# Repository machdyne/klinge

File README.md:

# Klinge Computer

Klinge is an FPGA computer designed by Lone Dynamics Corporation.

This repo contains schematics, PCB layouts, pinouts, a 3D-printable case, example gateware and documentation.

The 3D enclosure fits into a [Half10](https://github.com/machdyne/half10) compute bay, which can be used stand-alone or attached to a 10" rack.

Find more information on the [Klinge product page](https://machdyne.com/product/klinge-computer/).

## Programming Klinge

Klinge has a JTAG interface and ships with a [DFU bootloader](https://github.com/machdyne/tinydfu-bootloader) that allows the included flash [MMOD](https://machdyne.com/product/mmod) to be programmed over the USB-C port.

### DFU

The DFU bootloader is available for 5 seconds after power-on, issuing a DFU command during this period will stop the boot process until the DFU device is detached. If no command is received the boot process will continue and the user gateware will be loaded.

Install [dfu-util](http://dfu-util.sourceforge.net) (Debian/Ubuntu):

```
$ sudo apt install dfu-util
```

Update the user gateware on the flash MMOD:

```
$ sudo dfu-util -a 0 -D image.bit
```

Detach the DFU device and continue the boot process:

```
$ sudo dfu-util -a 0 -e
```

It is possible to update the bootloader itself using DFU but you shouldn't attempt this unless you have a JTAG programmer (or another method to program the MMOD) available, in case you need to restore the bootloader.

### JTAG

These examples assume you're using a "USB Blaster" JTAG cable, see the header pinout below. You will need to have [openFPGALoader](https://github.com/trabucayre/openFPGALoader) installed.

Program the configuration SRAM:

```
openFPGALoader -c usb-blaster image.bit
```

Program the flash MMOD:

```
openFPGALoader -f -c usb-blaster images/bootloader/tinydfu_klinge.bit
```

## Blinky 

Building the blinky example requires [Yosys](https://github.com/YosysHQ/yosys), [nextpnr-ecp5](https://github.com/YosysHQ/nextpnr) and [Project Trellis](https://github.com/YosysHQ/prjtrellis).

Assuming they are installed, you can simply type `make` to build the gateware, which will be written to output/blinky.bin. You can then use [openFPGALoader](https://github.com/trabucayre/openFPGALoader) or dfu-util to write the gateware to the device.

## Linux

See the [Kakao Linux](https://github.com/machdyne/kakao) repo for the latest instructions.

### Prebuilt Images

Copy the files from the `images/linux` directory to the root directory of a FAT-formatted MicroSD card.

Klinge ships with LiteX gateware on the user gateware section of the MMOD that is compatible with these images. After several seconds the Linux penguin should appear on the screen (HDMI) followed by a login prompt.

### Building Linux

Please follow the setup instructions in the [linux-on-litex-vexriscv](https://github.com/litex-hub/linux-on-litex-vexriscv) repo and then:

1. Build the Linux-capable gateware:

```
$ cd linux-on-litex-vexriscv
$ ./make.py --board klinge --uart-baudrate 115200 --build

$ ls build/klinge
```

2. Write the gateware to the MMOD using USB DFU:

```
$ sudo dfu-util -a 0 -D build/klinge/gateware/klinge.bit
```

3. Copy the device tree binary `build/klinge/klinge.dtb` to a FAT-formatted MicroSD card.

4. Build the Linux kernel and root filesystem:

See the [Kakao Linux](https://github.com/machdyne/kakao?tab=readme-ov-file#optional-building-kakao-linux) repo for instructions.

5. Copy the Image and rootfs.cpio files generated in the previous step to the boot partition of the MicroSD card, in addition to the following files:

6. Copy the OpenSBI binary (included in this repo as `klinge/images/linux/opensbi.bin`) to the MicroSD card. Alternatively, you can build this binary by following [these instructions](https://github.com/litex-hub/linux-on-litex-vexriscv#-generating-the-opensbi-binary-optional).

7. Copy `klinge/images/linux/boot.json` to the MicroSD card.

8. Power-cycle Klinge. After Linux has finished booting you should see a login prompt on the HDMI display.

## LiteX

### Installing LiteX

If you haven't yet installed LiteX please see the [LiteX quick start guide](https://github.com/enjoy-digital/litex#quick-start-guide) for details on installing LiteX.

### Building Custom Gateware

Build the LiteX gateware:

```
$ cd litex-boards/litex_boards/targets
$ ./machdyne_klinge.py --cpu-type=vexriscv --cpu-variant=lite --sys-clk-freq 40000000 --uart-baudrate 1000000 --uart-name serial --build
```

Program the LiteX gateware to SRAM over JTAG:

```
$ ./machdyne_klinge.py --cable usb-blaster --load
```

Or program the LiteX gateware to flash over DFU:

```
$ sudo dfu-util -a 0 -D build/machdyne_klinge/gateware/machdyne_klinge.bit
```

## JTAG Header

The 3.3V JTAG header can be used to program the FPGA SRAM as well as the MMOD flash memory. It can also be used to provide power (5V) to the board.

```
2 4 6
1 3 5
```

| Pin | Signal |
| --- | ------ |
| 1 | TCK |
| 2 | TDI |
| 3 | TDO |
| 4 | TMS |
| 5 | 5V0 |
| 6 | GND |

## Board Revisions

| Revision | Notes |
| -------- | ----- |
| V1 | Current production version |

## License

The contents of this repo are released under the [Lone Dynamics Open License](LICENSE.md).

Note: You can use these designs for commercial purposes but we ask that instead of producing exact clones, that you either replace our trademarks and logos with your own or add your own next to ours.

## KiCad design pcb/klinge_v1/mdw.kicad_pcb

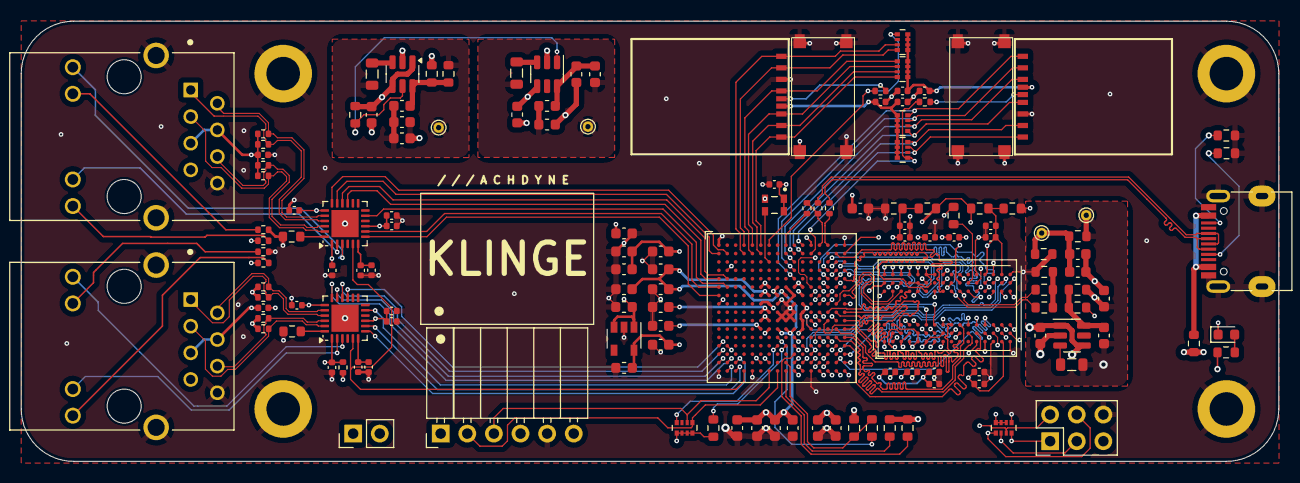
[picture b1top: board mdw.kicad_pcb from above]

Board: 6 copper layers, 120.0 x 42.0 mm, 143 parts (0 on the bottom side), 145 nets.

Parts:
C1, C2, C3, C4, C5, C6, C8, C9, C10, C13: 220nF; C_0603_1608Metric
C7, C11, C12, C15, C43: 1uF; C_0603_1608Metric
C14, C44, C48, C50, C54: 4.7uF; C_0603_1608Metric
C16, C64: 10uF; C_0402_1005Metric
C17, C19, C21, C22, C23, C26, C27, C32, C34, C35, C36, C37, C39, C47, C53, C59, C65: 100nF; C_0402_1005Metric
C18, C24, C29, C30, C33, C38, C41, C57: 1uF; C_0402_1005Metric
C20, C49: 470pF; C_0402_1005Metric
C25, C31: 22uF; R_0603_1608Metric
C28: 100nF; R_0603_1608Metric
C40, C60: 22nF; C_0402_1005Metric
C42: 100nF; C_0603_1608Metric
C45, C52, C61: 10pF; C_0603_1608Metric
C46, C56: 10uF; C_0603_1608Metric
C51, C55, C58, C62, C63: 22uF; C_0603_1608Metric
D1: LED; LED_0603_1608Metric
FB1, FB3, FB4: FerriteBead_Small; R_0603_1608Metric
FB2: FerriteBead_Small; R_0402_1005Metric
H1, H2, H3, H4: MountingHole_Pad; MountingHole_3.2mm_M3_ISO14580_Pad
J1: USB_C_Receptacle_USB2.0_14P; USB_C_Receptacle_HRO_TYPE-C-31-M-12-BIG-PADS-PASTE
J2, J4: MICROSD; TF-018B-H15-HAND-SOLDER
J3, J5: HR911105A; HANRUN_HR911105A
J6: Conn_01x02_Pin; PinHeader_1x02_P2.54mm_Vertical
JTAG1: Conn_02x03_Top_Bottom; PinHeader_2x03_P2.54mm_Vertical
L1, L2, L3: INDUCTOR; L_0805_2012Metric
MMOD1: PMOD-Device-x1-Type-2-SPI; MMOD_Host_Socket
R1, R2, R3: 4K7; R_0603_1608Metric
R4, R39, R40: 1K; R_0603_1608Metric
R6: 200K; R_0603_1608Metric
R7: 44K2; R_0603_1608Metric
R8, R47: 100R; R_0402_1005Metric
R9, R20, R21: 51R; R_0603_1608Metric
R11: 1K5; R_0603_1608Metric
R12, R31: 5K1; R_0603_1608Metric
R14: 240R; R_0603_1608Metric
R29: 536R; R_0603_1608Metric
R30, R59: 12K1; R_0603_1608Metric
R32, R33: 22R; R_0402_1005Metric
R34: 1K5; R_0402_1005Metric
R45: 150K; R_0603_1608Metric
R46, R53: 120K; R_0603_1608Metric
R51, R54, R55, R56, R60, R61, R62, R63: 49R9; R_0402_1005Metric
R52: 100K; R_0603_1608Metric
R57, R58, R64, R65: 536R; R_0402_1005Metric
RN1: 4K7; R_Array_Convex_4x0402
RN2, RN3, RN5, RN6: 20K; R_Array_Convex_4x0402
RN4: 10K; R_Array_Convex_4x0402
TP2: TP_DRAM_VREF; TestPoint_THTPad_D1.0mm_Drill0.5mm
TP3: TP_PWR1V35; TestPoint_THTPad_D1.0mm_Drill0.5mm
TP4: TP_PWR1V1; TestPoint_THTPad_D1.0mm_Drill0.5mm
TP5: TP_PWR3V3; TestPoint_THTPad_D1.0mm_Drill0.5mm
U1: Lattice_ECP_FPGA_ECP5U_45_CABGA256; BGA-256_14.0x14.0mm_Layout16x16_P0.8mm_Ball0.45mm_Pad0.32mm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
U3: MT41K64M16TW-107_J-TR; BGA-96_9.0x13.0mm_Layout2x3x16_P0.8mm_FIXED_SILK
U4, U5, U6: TLV62568DDC; SOT-23-6
U7, U10: LAN8720A; QFN-24-1EP_4x4mm_P0.5mm_EP2.6x2.6mm
U8: TLV73325PDBV; SOT-23-5
Y1: KC2016Z48; OSC_KC2016Z13.5600C1KX00

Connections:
/CFG_1: R1.2, U1.P10 (CFG_1)
/CSPI_MISO: MMOD1.3 (SO), RN4.2 (R2.1), U1.T7 (PB11A/+/D1/MISO/IO1)
/CSPI_MOSI: MMOD1.2 (SI), RN4.1 (R1.1), U1.T8 (PB11B/-/D0/MOSI/IO0)
/CSPI_SCK: MMOD1.4 (SCK), R4.2, U1.N9 (CCLK/MCLK/SCK)
/CSPI_SS: MMOD1.1 (SS), RN4.4 (R4.1), U1.N8 (PB15A/+/HOLDN/DI/BUSY/CSSPIN/CEN)
/DRAM_A0: U1.R15 (PR59C/+/RDQ65), U3.N3 (A0)
/DRAM_A1: U1.L13 (PR38C/+/GR_PCLK3_1/RDQ41), U3.P7 (A1)
/DRAM_A2: U1.P14 (PR59B/-/HS/RDQ65), U3.P3 (A2)
/DRAM_A3: U1.R14 (PR62B/-/HS/RDQ65), U3.N2 (A3)
/DRAM_A4: U1.L12 (PR38D/-/RDQ41), U3.P8 (A4)
/DRAM_A5: U1.T14 (PR62D/-/RDQ65), U3.P2 (A5)
/DRAM_A6: U1.N11 (PR68B/-/HS/RDQ65), U3.R8 (A6)
/DRAM_A7: U1.T13 (PR65B/-/HS/RDQSN65), U3.R2 (A7)
/DRAM_A8: U1.P12 (PR68D/-/LRC_GPLL0C_IN/RDQ65), U3.T8 (A8)
/DRAM_A9: U1.T15 (PR59D/-/RDQ65), U3.R3 (A9)
/DRAM_A10: U1.C14 (PR11C/+/RDQ17), U3.L7 (A10/AP)
/DRAM_A11: U1.M13 (PR44C/+/RDQ41), U3.R7 (A11)
/DRAM_A12: U1.E14 (PR14C/+/RDQ17), U3.N7 (A12/BC#)
/DRAM_A13: U1.R13 (PR62C/+/RDQ65), U3.T3 (A13)
/DRAM_A14: U1.M14 (PR41D/-/RDQ41), U3.T7 (A14)
/DRAM_A15: U1.D14 (PR11D/-/RDQ17), U3.M7 (A15)
/DRAM_BA0: U1.N16 (PR41A/+/HS/RDQS41), U3.M2 (BA0)
/DRAM_BA1: U1.K13 (PR38A/+/GR_PCLK3_0/HS/RDQ41), U3.N8 (BA1)
/DRAM_BA2: U1.P16 (PR44A/+/HS/RDQ41), U3.M3 (BA2)
/DRAM_CAS#: U1.M16 (PR35C/+/PCLKT3_0/RDQ41), U3.K3 (CAS#)
/DRAM_CKE: U1.K12 (PR38B/-/HS/RDQ41), U3.K9 (CKE)
/DRAM_CK_N: R21.2, U1.C15 (PR14B/-/HS/RDQ17), U3.K7 (CK#)
/DRAM_CK_P: R20.2, U1.C16 (PR14A/+/HS/RDQ17), U3.J7 (CK)
/DRAM_CS#: U1.M15 (PR35D/-/PCLKC3_0/RDQ41), U3.L2 (CS#)
/DRAM_DQ0: U1.F14 (PR14D/-/RDQ17), U3.E3 (DQ0)
/DRAM_DQ1: U1.E16 (PR20D/-/RDQ17), U3.F7 (DQ1)
/DRAM_DQ2: U1.F12 (PR17D/-/RDQ17), U3.F2 (DQ2)
/DRAM_DQ3: U1.F15 (PR20C/+/RDQ17), U3.F8 (DQ3)
/DRAM_DQ4: U1.G13 (PR20B/-/HS/RDQ17), U3.H3 (DQ4)
/DRAM_DQ5: U1.B16 (PR11A/+/URC_GPLL0T_IN/HS/RDQ17), U3.H8 (DQ5)
/DRAM_DQ6: U1.G12 (PR20A/+/HS/RDQ17), U3.G2 (DQ6)
/DRAM_DQ7: U1.B15 (PR11B/-/URC_GPLL0C_IN/HS/RDQ17), U3.H7 (DQ7)
/DRAM_DQ8: U1.J14 (PR29C/+/GR_PCLK2_0/RDQ29), U3.D7 (DQ8)
/DRAM_DQ9: U1.J16 (PR32A/+/PCLKT2_1/HS/RDQ29), U3.C3 (DQ9)
/DRAM_DQ10: U1.K15 (PR32D/-/PCLKC2_0/RDQ29), U3.C8 (DQ10)
/DRAM_DQ11: U1.K14 (PR29D/-/RDQ29), U3.C2 (DQ11)
/DRAM_DQ12: U1.H14 (PR23D/-/RDQ29), U3.A7 (DQ12)
/DRAM_DQ13: U1.K16 (PR32C/+/PCLKT2_0/RDQ29), U3.A2 (DQ13)
/DRAM_DQ14: U1.H13 (PR26B/-/HS/RDQ29), U3.B8 (DQ14)
/DRAM_DQ15: U1.J15 (PR32B/-/PCLKC2_1/HS/RDQ29), U3.A3 (DQ15)
/DRAM_LDM: U1.F13 (PR17C/+/RDQ17), U3.E7 (LDM)
/DRAM_LDQS_N: U1.E15 (PR17B/-/HS/RDQSN17), U3.G3 (LDQS#)
/DRAM_LDQS_P: U1.D16 (PR17A/+/HS/RDQS17), U3.F3 (LDQS)
/DRAM_ODT: U1.L15 (PR35B/-/PCLKC3_1/HS/RDQ41), U3.K1 (ODT)
/DRAM_RAS#: U1.L16 (PR35A/+/PCLKT3_1/HS/RDQ41), U3.J3 (RAS#)
/DRAM_RESET#: U1.R12 (PR65A/+/HS/RDQS65), U3.T2 (RESET#)
/DRAM_UDM: U1.J13 (PR26C/+/RDQ29), U3.D3 (UDM)
/DRAM_UDQS_N: U1.H15 (PR29B/-/HS/RDQSN29), U3.B7 (UDQS#)
/DRAM_UDQS_P: U1.G16 (PR29A/+/GR_PCLK2_1/HS/RDQS29), U3.C7 (UDQS)
/DRAM_VDD: C22.1, C23.1, C26.1, C27.1, C29.1, C30.1, C31.1, FB4.1, U3.B2 (VDD[9]), U3.D9 (VDD), U3.G7 (VDD), U3.K2 (VDD), U3.K8 (VDD), U3.N1 (VDD), U3.N9 (VDD), U3.R1 (VDD), U3.R9 (VDD)
/DRAM_VDDQ: C24.1, C25.1, C32.1, C34.1, C35.1, C37.1, C38.1, FB3.1, U3.A1 (VDDQ[9]), U3.A8 (VDDQ), U3.C1 (VDDQ), U3.C9 (VDDQ), U3.D2 (VDDQ), U3.E9 (VDDQ), U3.F1 (VDDQ), U3.H2 (VDDQ), U3.H9 (VDDQ)
/DRAM_VREF: C42.1, C43.1, R39.2, R40.1, TP2.1, U1.G14 (PR23C/+/VREF1_2/RDQ29), U1.R16 (PR44B/-/VREF1_3/HS/RDQ41), U3.H1 (VREFDQ), U3.M8 (VREFCA)
/DRAM_WE#: U1.P15 (PR41B/-/HS/RDQSN41), U3.L3 (WE#)
/DRAM_ZQ: R14.1, U3.L8 (ZQ)
/EA_LED1: J3.9, U7.3 (LED1/REGOFF)
/EA_LED2: J3.11, U7.2 (LED2/nINTSEL)
/EA_RX_N: J3.6, R51.2, U7.22 (RXN)
/EA_RX_P: J3.3, R54.2, U7.23 (RXP)
/EA_TX_N: J3.2, R55.2, U7.20 (TXN)
/EA_TX_P: J3.1, R56.2, U7.21 (TXP)
/EB_LED1: J5.9, U10.3 (LED1/REGOFF)
/EB_LED2: J5.11, U10.2 (LED2/nINTSEL)
/EB_RX_N: J5.6, R60.2, U10.22 (RXN)
/EB_RX_P: J5.3, R61.2, U10.23 (RXP)
/EB_TX_N: J5.2, R62.2, U10.20 (TXN)
/EB_TX_P: J5.1, R63.2, U10.21 (TXP)
/ETHA_CRS_DV: U1.F2 (PL20C/+/LDQ17), U7.11 (CRS_DV/MODE2)
/ETHA_RST_N: U1.E1 (PL20D/-/LDQ17), U7.15 (RST)
/ETHA_RX0: U1.F1 (PL23A/+/HS/LDQ29), U7.8 (RXD0/MODE0)
/ETHA_RX1: U1.G1 (PL29A/+/GR_PCLK7_1/HS/LDQS29), U7.7 (RXD1/MODE1)
/ETHA_TX0: U1.B1 (PL11A/+/ULC_GPLL0T_IN/HS/LDQ17), U7.17 (TXD0)
/ETHA_TX1: U1.B2 (PL11B/-/ULC_GPLL0C_IN/HS/LDQ17), U7.18 (TXD1)
/ETHA_TXEN: U1.E2 (PL17B/-/HS/LDQSN17), U7.16 (TXEN)
/ETHB_CRS_DV: U1.T2 (PL59D/-/LDQ65), U10.11 (CRS_DV/MODE2)
/ETHB_RST_N: U1.N1 (PL41A/+/HS/LDQS41), U10.15 (RST)
/ETHB_RX0: U1.T3 (PL62D/-/LDQ65), U10.8 (RXD0/MODE0)
/ETHB_RX1: U1.R3 (PL62B/-/HS/LDQ65), U10.7 (RXD1/MODE1)
/ETHB_TX0: U1.R1 (PL44B/-/VREF1_6/HS/LDQ41), U10.17 (TXD0)
/ETHB_TX1: U1.R2 (PL59C/+/LDQ65), U10.18 (TXD1)
/ETHB_TXEN: U1.P1 (PL44A/+/HS/LDQ41), U10.16 (TXEN)
/ETH_CLK50: U1.T4 (PL65B/-/HS/LDQSN65), U7.5 (XTAL1/CLKIN), U10.5 (XTAL1/CLKIN)
/INITN: R2.2, U1.T9 (INITN)
/JTAG_TCK: JTAG1.1, RN1.4 (R4.1), U1.T10 (TCK)
/JTAG_TDI: JTAG1.2, RN1.3 (R3.1), U1.R11 (TDI)
/JTAG_TDO: JTAG1.3, RN1.2 (R2.1), U1.M10 (TDO)
/JTAG_TMS: JTAG1.4, RN1.1 (R1.1), U1.T11 (TMS)
/LED: D1.1 (K), U1.A12 (PT71B/-)
/PROGRAMN: R3.2, R9.2, U1.R9 (PROGRAMN)
/PWR1V1: C2.2, C4.2, C9.2, C10.2, C11.2, C12.2, C51.1, C52.1, C55.1, C56.1, L2.2, R52.1, TP4.1, U1.G6 (VCC[6]), U1.G7 (VCC[6]), U1.G9 (VCC[6]), U1.L8 (VCC[6]), U1.L9 (VCC[6]), U1.L10 (VCC[6])
/PWR1V35: C13.2, C15.2, C45.1, C46.1, FB3.2, FB4.2, L1.2, R39.1, R45.1, TP3.1, U1.H11 (VCCIO2[2]), U1.J11 (VCCIO2[2]), U1.K11 (VCCIO3[2]), U1.L11 (VCCIO3[2])
/PWR2V5: C3.2, C54.1, U1.G11 (VCCAUX[2]), U1.H6 (VCCIO7[2]), U1.H7 (VCCIO7[2]), U1.L7 (VCCAUX[2]), U8.5 (OUT)
/PWR3V3: C1.2, C5.2, C6.2, C7.2, C8.2, C16.1, C17.1, C18.1, C19.1, C39.1, C41.1, C47.1, C50.1, C58.1, C61.1, C62.1, C63.1, C64.1, C65.1, FB2.2, J2.4 (VDD), J4.4 (VDD), L3.2, MMOD1.6 (VCC), R1.1, R2.1, R3.1, R4.1, R6.1, R29.1, RN1.6 (R3.2), RN1.7 (R2.2), RN1.8 (R1.2), RN2.1 (R1.1), RN2.2 (R2.1), RN2.3 (R3.1), RN2.4 (R4.1), RN3.1 (R1.1), RN3.2 (R2.1), RN3.3 (R3.1), RN3.4 (R4.1), RN4.5 (R4.2), RN4.6 (R3.2), RN4.7 (R2.2), RN4.8 (R1.2), RN5.1 (R1.1), RN5.2 (R2.1), RN5.3 (R3.1), RN5.4 (R4.1), RN6.1 (R1.1), RN6.2 (R2.1), RN6.3 (R3.1), RN6.4 (R4.1), TP5.1, U1.F6 (VCCIO0[2]), U1.F7 (VCCIO0[2]), U1.F10 (VCCIO1[2]), U1.F11 (VCCIO1[2]), U1.J6 (VCCIO6[2]), U1.J7 (VCCIO6[2]), U1.L6 (VCCIO8), U7.9 (VDDIO), U8.1 (IN), U8.3 (EN), U10.9 (VDDIO), Y1.1 (INH), Y1.4 (VCC)
/PWR3V3A: C21.1, C36.1, C40.1, C53.1, C59.1, C60.1, FB2.1, J3.4, J3.5, J5.4, J5.5, R51.1, R54.1, R55.1, R56.1, R58.1, R60.1, R61.1, R62.1, R63.1, R65.1, U7.1 (VDD2A), U7.19 (VDD1A), U10.1 (VDD2A), U10.19 (VDD1A)
/PWR5V0: C14.1, C44.1, C48.1, FB1.2, JTAG1.5, R11.2, U4.1 (EN), U4.4 (VIN), U5.1 (EN), U5.4 (VIN), U6.4 (VIN)
/SDA_CD: R47.1, RN2.5 (R4.2), U1.A7 (PT38A/+/PCLKT0_0)
/SDA_D1: J4.8 (DAT1), RN2.7 (R2.2), U1.B4 (PT11B/-)
/SDA_D2: J4.1 (DAT2), RN3.8 (R1.2), U1.A6 (PT18B/-)
/SDA_MISO: J4.7 (DAT0), RN2.8 (R1.2), U1.A4 (PT6B/-)
/SDA_MOSI: J4.3 (CMD), RN3.6 (R3.2), U1.A5 (PT18A/+)
/SDA_SCK: J4.5 (CLK), RN3.5 (R4.2), U1.B5 (PT15B/-)
/SDA_SS: J4.2 (DAT3/CD), RN3.7 (R2.2), U1.B6 (PT31B/-)
/SDB_CD: R8.1, RN6.5 (R4.2), U1.B12 (PT74A/+)
/SDB_D1: J2.8 (DAT1), RN6.7 (R2.2), U1.A11 (PT71A/+)
/SDB_D2: J2.1 (DAT2), RN5.8 (R1.2), U1.E10 (PT56B/-)
/SDB_MISO: J2.7 (DAT0), RN6.8 (R1.2), U1.B11 (PT58A/+)
/SDB_MOSI: J2.3 (CMD), RN5.6 (R3.2), U1.C10 (PT53B/-)
/SDB_SCK: J2.5 (CLK), RN5.5 (R4.2), U1.B10 (PT53A/+)
/SDB_SS: J2.2 (DAT3/CD), RN5.7 (R2.2), U1.D10 (PT56A/+)
/SYS_CLK48: U1.C7 (PT36A/+/PCLKT0_1), Y1.3 (OUTPUT)
/SYS_PG: R11.1, U4.5 (PG), U6.1 (EN)
/SYS_RST_N: R9.1, U1.M8 (PB15B/-/DOUT/CSON)
/UART_RX: J6.2, U1.R7 (PB6A/+/D5/MISO2/IO5)
/UART_TX: J6.1, U1.R6 (PB4B/-/D6/IO6)
/USBDC_CC1: J1.A5 (CC1), R12.1
/USBDC_CC2: J1.B5 (CC2), R31.1
/USBDC_N: J1.A7 (D-), J1.B7 (D-), R33.1
/USBDC_P: J1.A6 (D+), J1.B6 (D+), R32.1
/USBDC_VBUS: FB1.1, J1.A4 (VBUS), J1.A9 (VBUS), J1.B4 (VBUS), J1.B9 (VBUS)
/USBD_N: R33.2, U1.A14 (PT83B/-)
/USBD_P: R32.2, R34.2, U1.A13 (PT83A/+)
/USBD_PU: R34.1, U1.A9 (PT51A/+)
GND: C1.1, C2.1, C3.1, C4.1, C5.1, C6.1, C7.1, C8.1, C9.1, C10.1, C11.1, C12.1, C13.1, C14.2, C15.1, C16.2, C17.2, C18.2, C19.2, C20.2, C21.2, C22.2, C23.2, C24.2, C25.2, C26.2, C27.2, C28.2, C29.2, C30.2, C31.2, C32.2, C33.2, C34.2, C35.2, C36.2, C37.2, C38.2, C39.2, C40.2, C41.2, C42.2, C43.2, C44.2, C46.2, C47.2, C48.2, C49.2, C50.2, C51.2, C53.2, C54.2, C55.2, C56.2, C57.2, C58.2, C59.2, C60.2, C62.2, C63.2, C64.2, C65.2, H1.1, H2.1, H3.1, H4.1, J1.A1 (GND), J1.A12 (GND), J1.B1 (GND), J1.B12 (GND), J1.S1 (SHIELD), J2.6 (VSS), J3.8, J3.15 (SHIELD), J3.16 (SHIELD), J4.6 (VSS), J5.8, J5.15 (SHIELD), J5.16 (SHIELD), JTAG1.6, MMOD1.5 (GND), R7.2, R12.2, R14.2, R30.1, R31.2, R40.2, R46.2, R53.2, R57.1, R59.1, R64.1, RN1.5 (R4.2), U1.A1 (GND[27]), U1.A16 (GND[27]), U1.D2 (GND[27]), U1.D15 (GND[27]), U1.F8 (GND[27]), U1.F9 (GND[27]), U1.G8 (GND[27]), U1.G10 (GND[27]), U1.H1 (GND[27]), U1.H8 (GND[27]), U1.H9 (GND[27]), U1.H10 (GND[27]), U1.H16 (GND[27]), U1.J8 (GND[27]), U1.J9 (GND[27]), U1.J10 (GND[27]), U1.K6 (GND[27]), U1.K7 (GND[27]), U1.K8 (GND[27]), U1.K9 (GND[27]), U1.K10 (GND[27]), U1.N2 (GND[27]), U1.N10 (CFG_0), U1.N15 (GND[27]), U1.R10 (CFG_2), U1.T1 (GND[27]), U1.T5 (GND[27]), U1.T12 (GND[27]), U1.T16 (GND[27]), U3.A9 (VSS[12]), U3.B1 (VSSQ[9]), U3.B3 (VSS), U3.B9 (VSSQ), U3.D1 (VSSQ), U3.D8 (VSSQ), U3.E1 (VSS), U3.E2 (VSSQ), U3.E8 (VSSQ), U3.F9 (VSSQ), U3.G1 (VSSQ), U3.G9 (VSSQ), U3.J2 (VSS), U3.J8 (VSS), U3.M1 (VSS), U3.M9 (VSS), U3.P1 (VSS), U3.P9 (VSS), U3.T1 (VSS), U3.T9 (VSS), U4.2 (GND), U5.2 (GND), U6.2 (GND), U7.25 (VSS), U8.2 (GND), U10.25 (VSS), Y1.2 (CASE_GND)
unnamed: C28.1, R20.1, R21.1
unnamed: D1.2 (A), R29.2
unnamed: J2.9 (DET_B), R8.2
unnamed: J3.10, R57.2
unnamed: J3.12, R58.2
unnamed: J4.9 (DET_B), R47.2
unnamed: J5.10, R64.2
unnamed: J5.12, R65.2
unnamed: C61.2, R6.2, R7.1, U4.6 (FB)
unnamed: L3.1, U4.3 (SW)
unnamed: C45.2, R45.2, R46.1, U5.6 (FB)
unnamed: L1.1, U5.3 (SW)
unnamed: C52.2, R52.2, R53.1, U6.6 (FB)
unnamed: L2.1, U6.3 (SW)
unnamed: R30.2, U7.24 (RBIAS)
unnamed: C20.1, C33.1, U7.6 (VDDCR)
unnamed: R59.2, U10.24 (RBIAS)
unnamed: C49.1, C57.1, U10.6 (VDDCR)

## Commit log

2025-03-28 add pcb
2025-06-02 add klinge stands
2025-06-02 add usb dfu bootloader
2025-06-02 dual microsd support
